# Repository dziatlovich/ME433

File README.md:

# Welcome to ME433 Homeworks Repository by Maksim Dziatlovich

This is very much work in progress. Homeworks up to HW4 will be submitted by April, 18.

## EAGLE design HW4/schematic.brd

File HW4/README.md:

# Homework 4

- Schematic - [Link](https://github.com/dziatlovich/ME433/blob/master/HW4/eagle_K7oHcYi7Ng.png)
- Board - [Link](https://github.com/dziatlovich/ME433/blob/master/HW4/eagle_mVcaXFvITx.png)

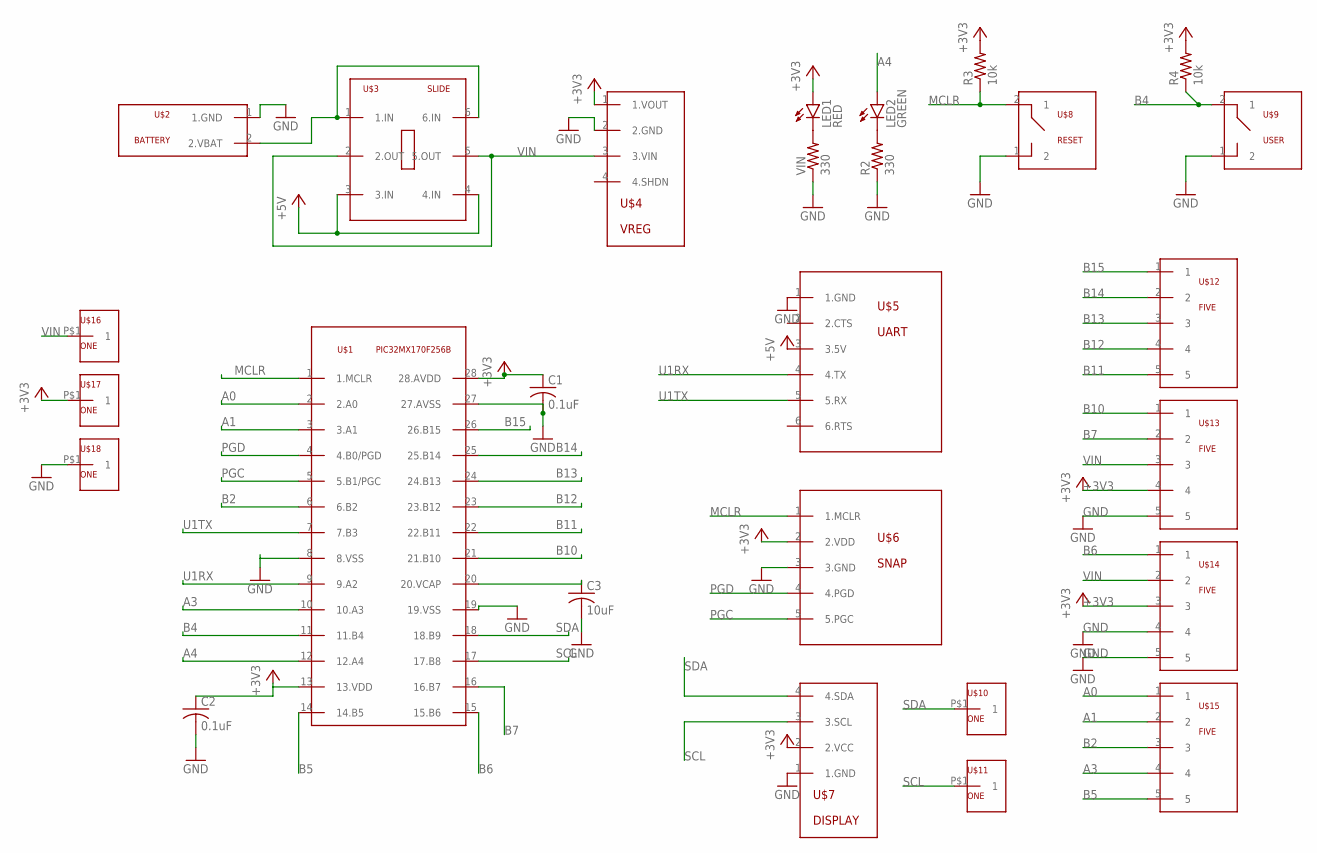
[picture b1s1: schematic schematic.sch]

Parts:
C1, C2: 0.1uF; C025-024X044
C3: 10uF; C025-024X044
LED1: RED; LED3MM
LED2: GREEN; LED3MM
R2: 330; 0207/7
R3, R4: 10k; 0207/7
U$1: PIC32MX170F256B; DIL28-3
U$2: BATTERY
U$3: SLIDE
U$4: VREG
U$5: UART; USBUART
U$6: SNAP
U$7: DISPLAY
U$8: RESET; PUSH
U$9: USER; PUSH
U$10, U$11, U$16, U$17, U$18: ONE
U$12, U$13, U$14, U$15: FIVE
VIN: 330; 0207/7

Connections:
+3V3: C1.1, C2.1, LED1.A, R3.2, R4.2, U$1.13 (13.VDD), U$1.28 (28.AVDD), U$4.1 (1.VOUT), U$6.2 (2.VDD), U$7.2 (2.VCC), U$13.4, U$14.3, U$17.P$1
+5V: U$3.3 (3.IN), U$3.4 (4.IN), U$5.3 (3.5V)
A0: U$1.2 (2.A0), U$15.1
A1: U$1.3 (3.A1), U$15.2
A3: U$1.10 (10.A3), U$15.4
A4: LED2.A, U$1.12 (12.A4)
B2: U$1.6 (6.B2), U$15.3
B4: R4.1, U$1.11 (11.B4), U$9.2 (1)
B5: U$1.14 (14.B5), U$15.5
B6: U$1.15 (15.B6), U$14.1
B7: U$1.16 (16.B7), U$13.2
B10: U$1.21 (21.B10), U$13.1
B11: U$1.22 (22.B11), U$12.5
B12: U$1.23 (23.B12), U$12.4
B13: U$1.24 (24.B13), U$12.3
B14: U$1.25 (25.B14), U$12.2
B15: U$1.26 (26.B15), U$12.1
GND: C1.2, C2.2, C3.2, R2.1, U$1.8 (8.VSS), U$1.19 (19.VSS), U$1.27 (27.AVSS), U$2.1 (1.GND), U$4.2 (2.GND), U$5.1 (1.GND), U$6.3 (3.GND), U$7.1 (1.GND), U$8.1 (2), U$9.1 (2), U$13.5, U$14.4, U$14.5, U$18.P$1, VIN.1
MCLR: R3.1, U$1.1 (1.MCLR), U$6.1 (1.MCLR), U$8.2 (1)
unnamed: LED1.K (C), VIN.2
unnamed: LED2.K (C), R2.2
unnamed: U$2.2 (2.VBAT), U$3.1 (1.IN), U$3.6 (6.IN)
unnamed: C3.1, U$1.20 (20.VCAP)
PGC: U$1.5 (5.B1/PGC), U$6.5 (5.PGC)
PGD: U$1.4 (4.B0/PGD), U$6.4 (4.PGD)
SCL: U$1.17 (17.B8), U$7.3 (3.SCL), U$11.P$1
SDA: U$1.18 (18.B9), U$7.4 (4.SDA), U$10.P$1
U1RX: U$1.9 (9.A2), U$5.4 (4.TX)
U1TX: U$1.7 (7.B3), U$5.5 (5.RX)
VIN: U$3.2 (2.OUT), U$3.5 (5.OUT), U$4.3 (3.VIN), U$13.3, U$14.2, U$16.P$1

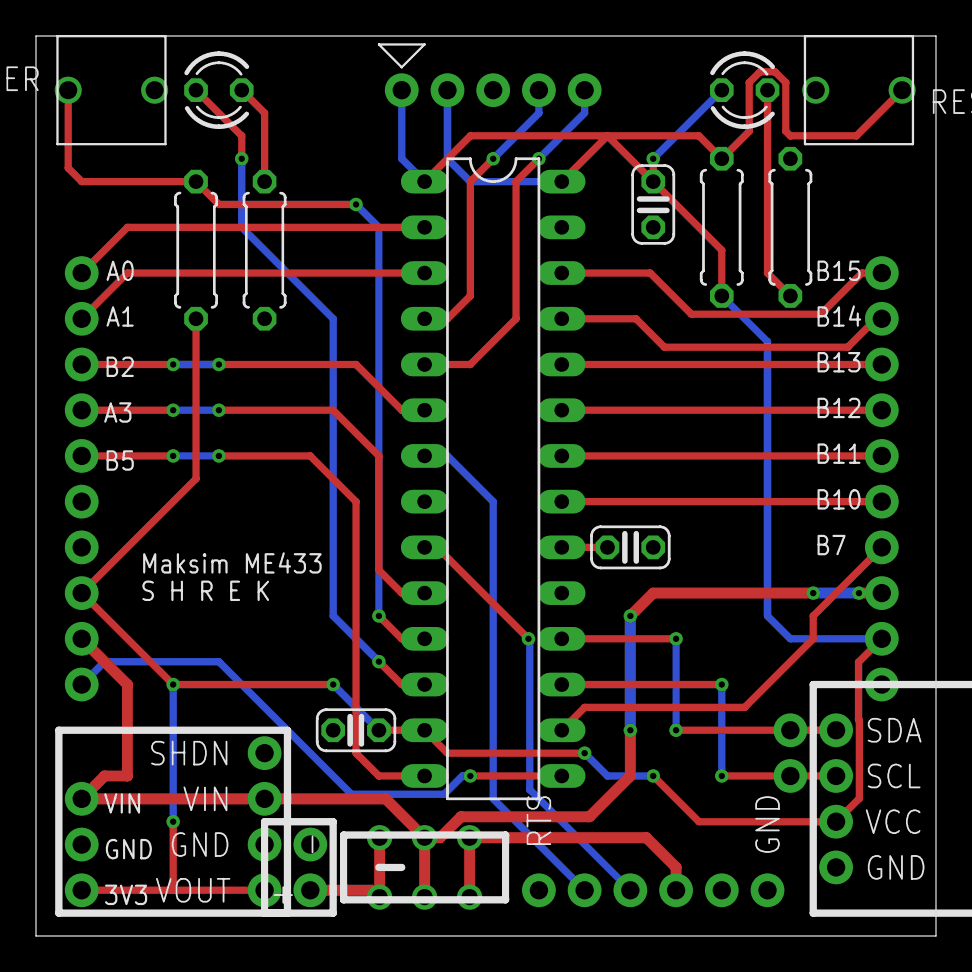
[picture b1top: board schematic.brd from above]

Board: 2 copper layers, 50.0 x 50.0 mm, 27 parts (0 on the bottom side), 30 nets.

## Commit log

2022-06-09 repo clean up
2022-06-09 a few tweeks to hw6 code
2022-06-09 tweaks
